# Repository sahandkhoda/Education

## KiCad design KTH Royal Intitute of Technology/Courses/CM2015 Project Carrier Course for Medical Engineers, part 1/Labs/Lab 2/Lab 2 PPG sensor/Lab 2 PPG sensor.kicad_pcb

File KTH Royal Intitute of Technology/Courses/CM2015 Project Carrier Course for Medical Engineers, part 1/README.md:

# CM2015 – Project Carrier Course for Medical Engineers, part 1

**Course overview**

This course provides theoretical knowledge and practical skills in project carrier course for medical engineers, part 1. Students develop analytical thinking, engineering problem-solving abilities, and experience applying concepts through assignments, laboratory work, projects, or examinations.

**Key learning outcomes**
- Understand the core principles and methods of the subject.
- Apply engineering tools and techniques to solve relevant problems.
- Strengthen analytical, technical, and communication skills.
- Build competencies that are directly applicable in engineering and technology roles.

This course is part of the KTH curriculum and contributes to a solid foundation for professional engineering practice and further specialization.

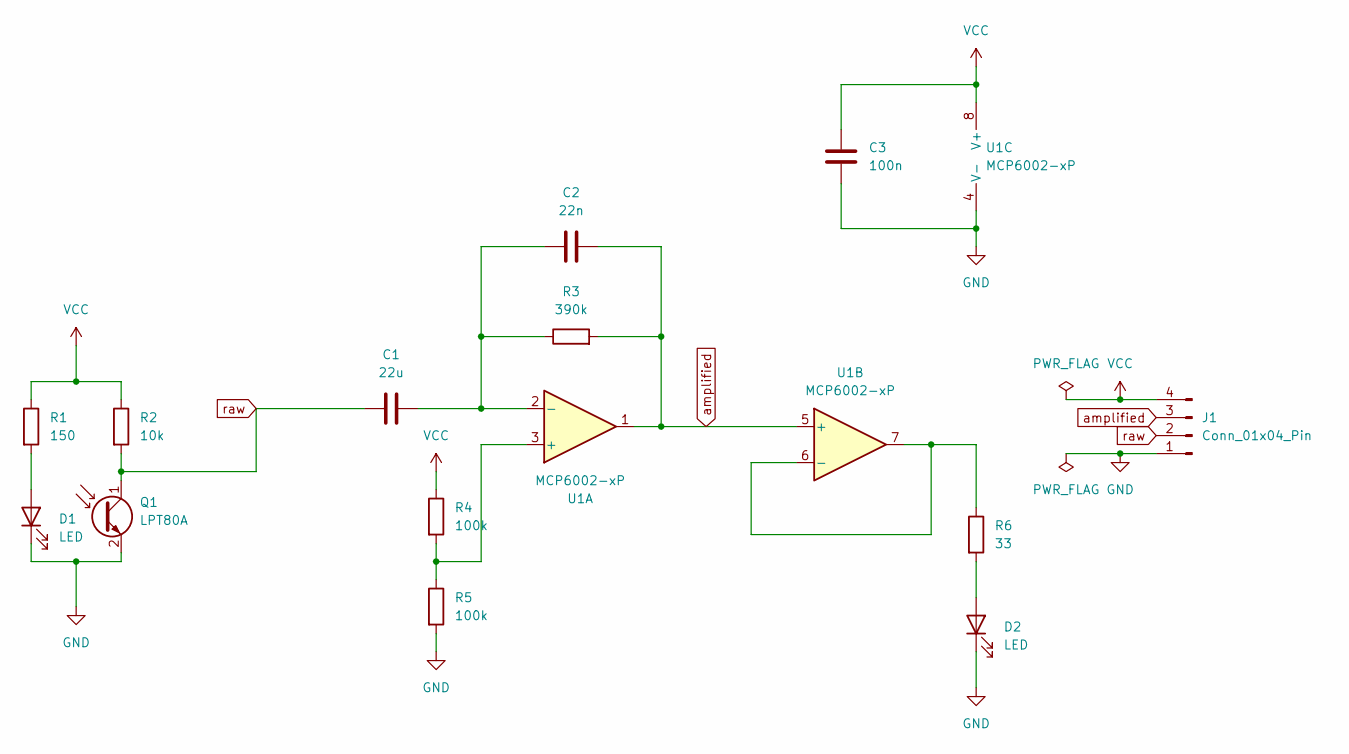
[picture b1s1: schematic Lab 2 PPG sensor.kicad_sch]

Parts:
C1: 22u; C_0805_2012Metric_Pad1.18x1.45mm_HandSolder
C2: 22n; C_0805_2012Metric_Pad1.18x1.45mm_HandSolder
C3: 100n; C_0805_2012Metric_Pad1.18x1.45mm_HandSolder
D1, D2: LED; LED_D5.0mm
J1: Conn_01x04_Pin; PinHeader_1x04_P2.54mm_Vertical
Q1: LPT80A; Osram_LPT80A
R1: 150; R_Axial_DIN0207_L6.3mm_D2.5mm_P10.16mm_Horizontal
R2: 10k; R_Axial_DIN0207_L6.3mm_D2.5mm_P10.16mm_Horizontal
R3: 390k; R_Axial_DIN0207_L6.3mm_D2.5mm_P10.16mm_Horizontal
R4, R5: 100k; R_Axial_DIN0207_L6.3mm_D2.5mm_P10.16mm_Horizontal
R6: 33; R_Axial_DIN0207_L6.3mm_D2.5mm_P10.16mm_Horizontal
U1: MCP6002-xP; DIP-8_W7.62mm_LongPads

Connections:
GND: C3.2, D1.1 (K), D2.1 (K), J1.1, Q1.2 (E), R5.2, U1.4 (V-)
unnamed: D1.2 (A), R1.2
unnamed: D2.2 (A), R6.2
unnamed: R4.2, R5.1, U1.3 (+)
unnamed: C1.2, C2.1, R3.1, U1.2 (-)
unnamed: R6.1, U1.6 (-), U1.7
VCC: C3.1, J1.4, R1.1, R2.1, R4.1, U1.8 (V+)
amplified: C2.2, J1.3, R3.2, U1.1, U1.5 (+)
raw: C1.1, J1.2, Q1.1 (C), R2.2

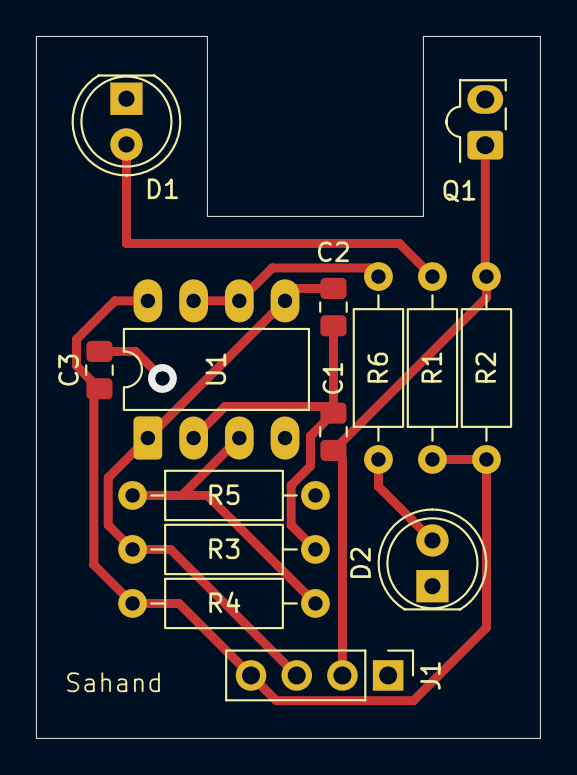
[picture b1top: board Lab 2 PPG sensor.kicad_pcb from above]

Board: 2 copper layers, 28.0 x 39.0 mm, 14 parts (0 on the bottom side), 9 nets.
